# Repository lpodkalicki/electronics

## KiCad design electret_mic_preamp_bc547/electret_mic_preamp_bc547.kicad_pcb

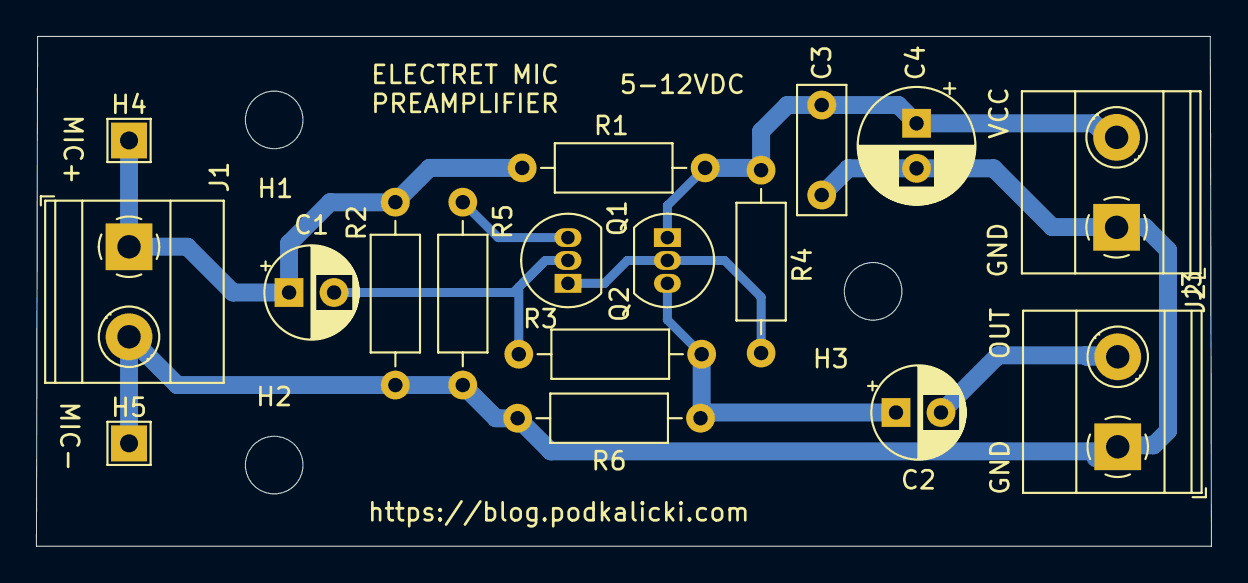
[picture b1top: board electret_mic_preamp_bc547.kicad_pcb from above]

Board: 2 copper layers, 65.3 x 28.3 mm, 20 parts (0 on the bottom side), 8 nets.

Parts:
C1: 2u2; CP_Radial_D5.0mm_P2.50mm
C2: 4u7; CP_Radial_D5.0mm_P2.50mm
C3: 100n; C_Rect_L7.0mm_W2.5mm_P5.00mm
C4: 100u; CP_Radial_D6.3mm_P2.50mm
H1, H2, H3: MountingHole; MountingHole_3.2mm_M3_DIN965
H4: MIC+; TestPoint_THTPad_2.0x2.0mm_Drill1.0mm
H5: MIC-; TestPoint_THTPad_2.0x2.0mm_Drill1.0mm
J1: INPUT; TerminalBlock_Phoenix_MKDS-1,5-2_1x02_P5.00mm_Horizontal
J2: POWER; TerminalBlock_Phoenix_MKDS-1,5-2_1x02_P5.00mm_Horizontal
J3: OUTPUT; TerminalBlock_Phoenix_MKDS-1,5-2_1x02_P5.00mm_Horizontal
Q1, Q2: BC547C; TO-92_Inline
R1: Rx; R_Axial_DIN0207_L6.3mm_D2.5mm_P10.16mm_Horizontal
R2: Ry; R_Axial_DIN0207_L6.3mm_D2.5mm_P10.16mm_Horizontal
R3: 330k; R_Axial_DIN0207_L6.3mm_D2.5mm_P10.16mm_Horizontal
R4, R6: 10k; R_Axial_DIN0207_L6.3mm_D2.5mm_P10.16mm_Horizontal
R5: 120; R_Axial_DIN0207_L6.3mm_D2.5mm_P10.16mm_Horizontal

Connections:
GND: C3.2, C4.2, H5.1, J1.2, J2.1, J3.1, R2.2, R5.2, R6.2
unnamed: C1.1, H4.1, J1.1, R1.2, R2.1
unnamed: C1.2, Q1.2, R3.2
unnamed: C2.1, Q2.3, R3.1, R6.1
unnamed: C2.2, J3.2
unnamed: Q1.1, Q2.2, R4.2
unnamed: Q1.3, R5.1
VCC: C3.1, C4.1, J2.2, Q2.1, R1.1, R4.1

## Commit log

2020-10-20 Add project - electret mic preamp based on bc547.
